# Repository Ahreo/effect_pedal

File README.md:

# effect_pedal

Guitar effect pedal with bluetooth connectivity!

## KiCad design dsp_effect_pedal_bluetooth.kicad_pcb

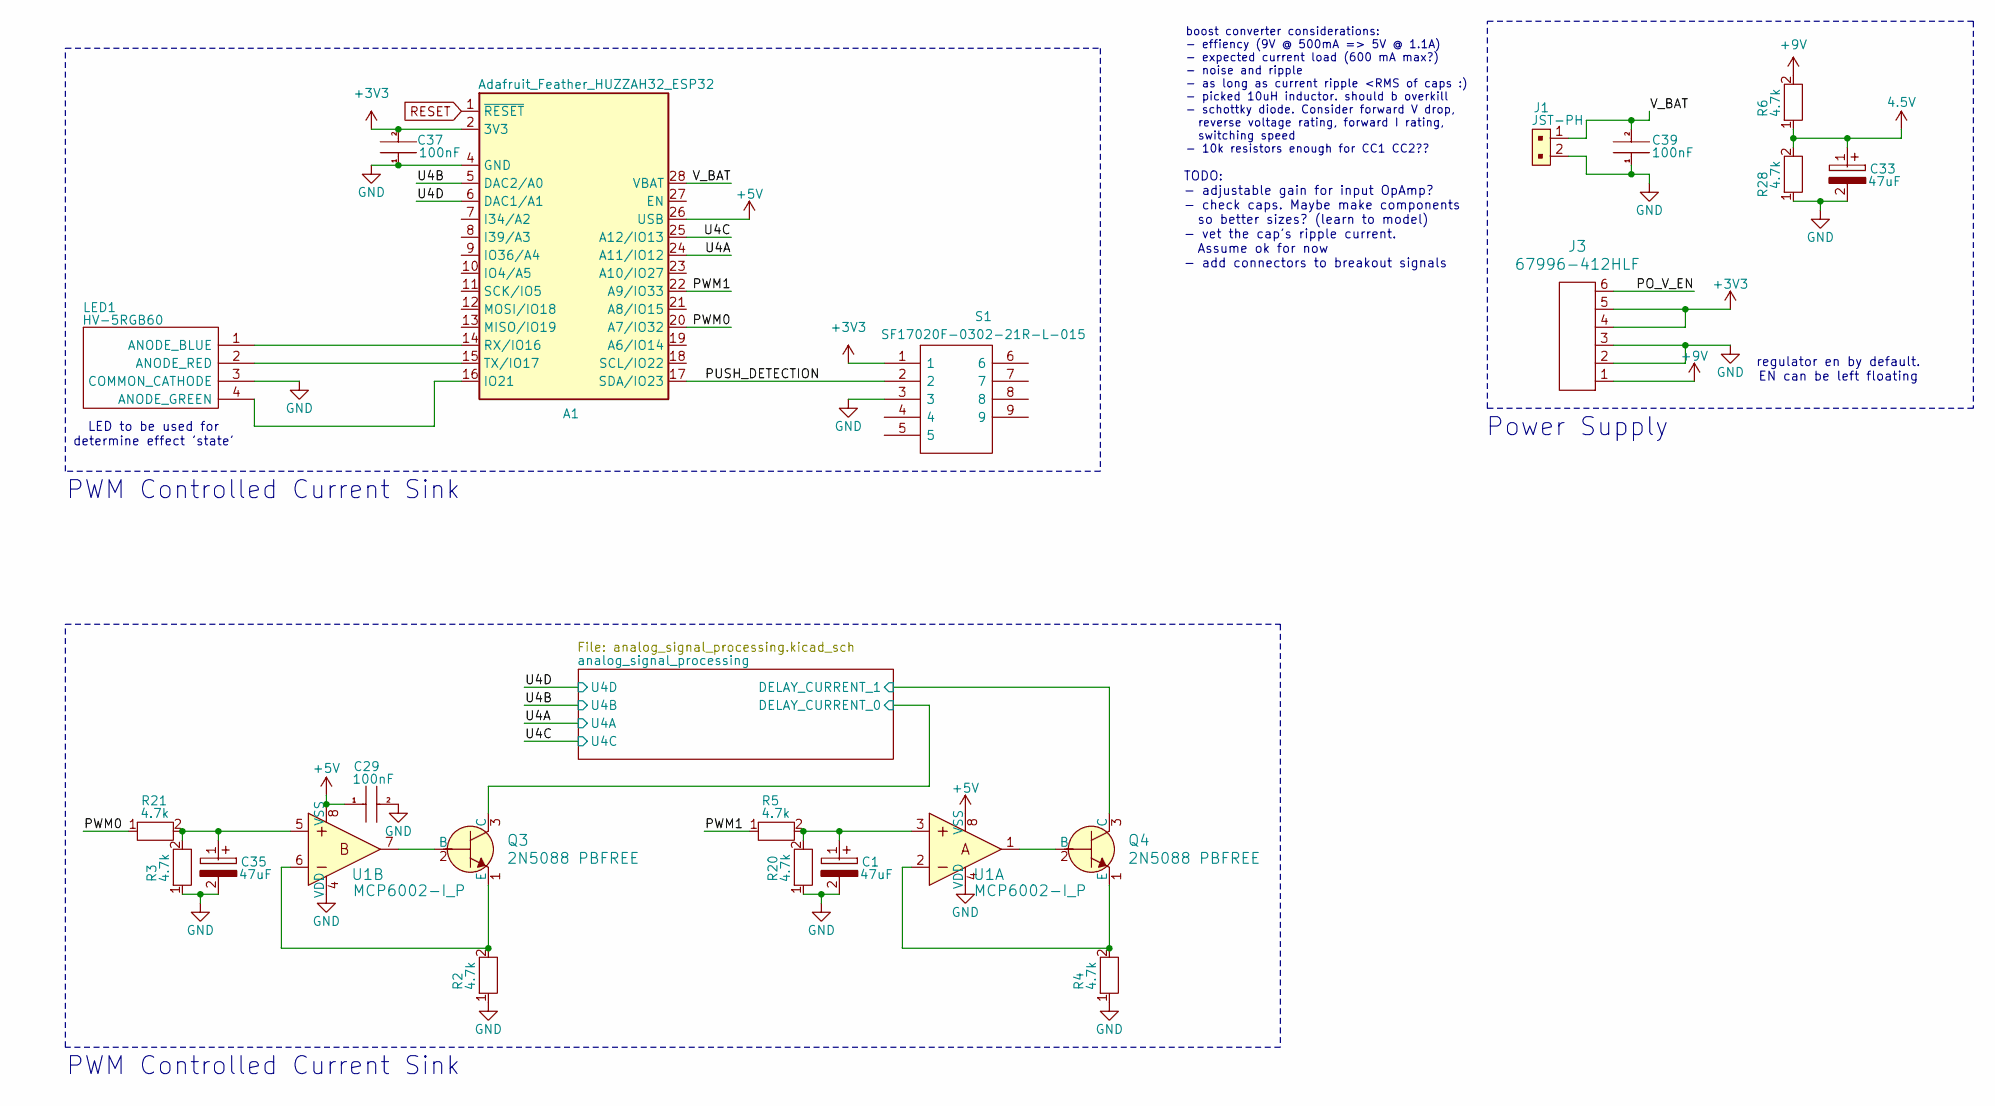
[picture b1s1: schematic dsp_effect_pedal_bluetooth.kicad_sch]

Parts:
A1: Adafruit_Feather_HUZZAH32_ESP32; Adafruit_Feather
C1, C33, C35: 47uF; 1206; Manufacturer_Part_Number REA470M1CBK-0511P; Mouser Part Number 140-REA470M1CBK0511P
C29, C37, C39: 100nF; 1206; Manufacturer_Part_Number SR211C104KARTR1; Mouser Part Number 581-SR211C104KARTR1
J1: JST-PH; PinHeader_1x2_P2mm_Drill1mm; MPN B2B-PH-K-S(LF)(SN); Digi-Key_PN 455-1704-ND
J3: 67996-412HLF; PinHeader_1x06_P2.54mm_Vertical; MPN 67996-412HLF; Digi-Key_PN 609-3219-ND
LED1: HV-5RGB60; HV5RGB25; Manufacturer_Part_Number HV-5RGB60; Mouser Part Number 743-HV-5RGB60
Q3, Q4: 2N5088 PBFREE; TO-92-3; MPN 2N5088BU; Digi-Key_PN 2N5088BU-ND
R2, R3, R4, R5, R6, R20, R21, R28: 4.7k; 1206; Manufacturer_Part_Number MFR-25FRF52-4K7; Mouser Part Number 603-MFR-25FRF52-4K7
S1: SF17020F-0302-21R-L-015; SF17020F030221RL015; Manufacturer_Part_Number SF17020F-0302-21R-L-015; Mouser Part Number 107-SF17020F-32-21RL
U1: MCP6002-I_P; DIP-8_W7.62mm; MPN MCP6002-I/P; Digi-Key_PN MCP6002-I/P-ND

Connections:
4.5V: C33.1, R6.1, R28.2; also elsewhere on the board
+3V3: A1.2 (3V3), C37.2, J3.4, J3.5, S1.1
+5V: A1.26 (USB), C29.1, U1.8 (VSS); also elsewhere on the board
+9V: J3.1, R6.2; also elsewhere on the board
/PO_V_EN: J3.6
/PUSH_DETECTION: A1.17 (SDA/IO23), S1.2
/PWM0: A1.20 (A7/IO32), R21.1
/PWM1: A1.22 (A9/IO33), R5.1
/U4A: A1.24 (A11/IO12); also elsewhere on the board
/U4B: A1.5 (DAC2/A0); also elsewhere on the board
/U4C: A1.25 (A12/IO13); also elsewhere on the board
/U4D: A1.6 (DAC1/A1); also elsewhere on the board
/V_BAT: A1.28 (VBAT), C39.2, J1.1
/analog_signal_processing/DELAY_CURRENT_0: Q3.3 (C); also elsewhere on the board
/analog_signal_processing/DELAY_CURRENT_1: Q4.3 (C); also elsewhere on the board
GND: A1.4 (GND), C1.2, C29.2, C33.2, C35.2, C37.1, C39.1, J1.2, J3.2, J3.3, LED1.3 (COMMON_CATHODE), R2.1, R3.1, R4.1, R20.1, R28.1, S1.3, U1.4 (VDD); also elsewhere on the board
unnamed: A1.16 (IO21), LED1.4 (ANODE_GREEN)
unnamed: A1.14 (RX/IO16), LED1.1 (ANODE_BLUE)
unnamed: A1.15 (TX/IO17), LED1.2 (ANODE_RED)
unnamed: C1.1, R5.2, R20.2, U1.3
unnamed: C35.1, R3.2, R21.2, U1.5
unnamed: Q3.2 (B), U1.7
unnamed: Q3.1 (E), R2.2, U1.6
unnamed: Q4.2 (B), U1.1
unnamed: Q4.1 (E), R4.2, U1.2
RESET: A1.1 (~RESET)

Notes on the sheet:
PWM Controlled Current Sink
LED to be used for determine effect 'state'
Power Supply
boost converter considerations: - effiency (9V @ 500mA => 5V @ 1.1A) - expected current load (600 mA max?) - noise and ripple - as long as current ripple <RMS of caps :) - picked 10uH inductor. should b overkill - schottky diode. Consider forward V drop, reverse voltage rating, forward I rating, sw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
regulator en by default. EN can be left floating
TODO: - adjustable gain for input OpAmp? - check caps. Maybe make components so better sizes? (learn to model) - vet the cap's ripple current. Assume ok for now - add connectors to breakout signals

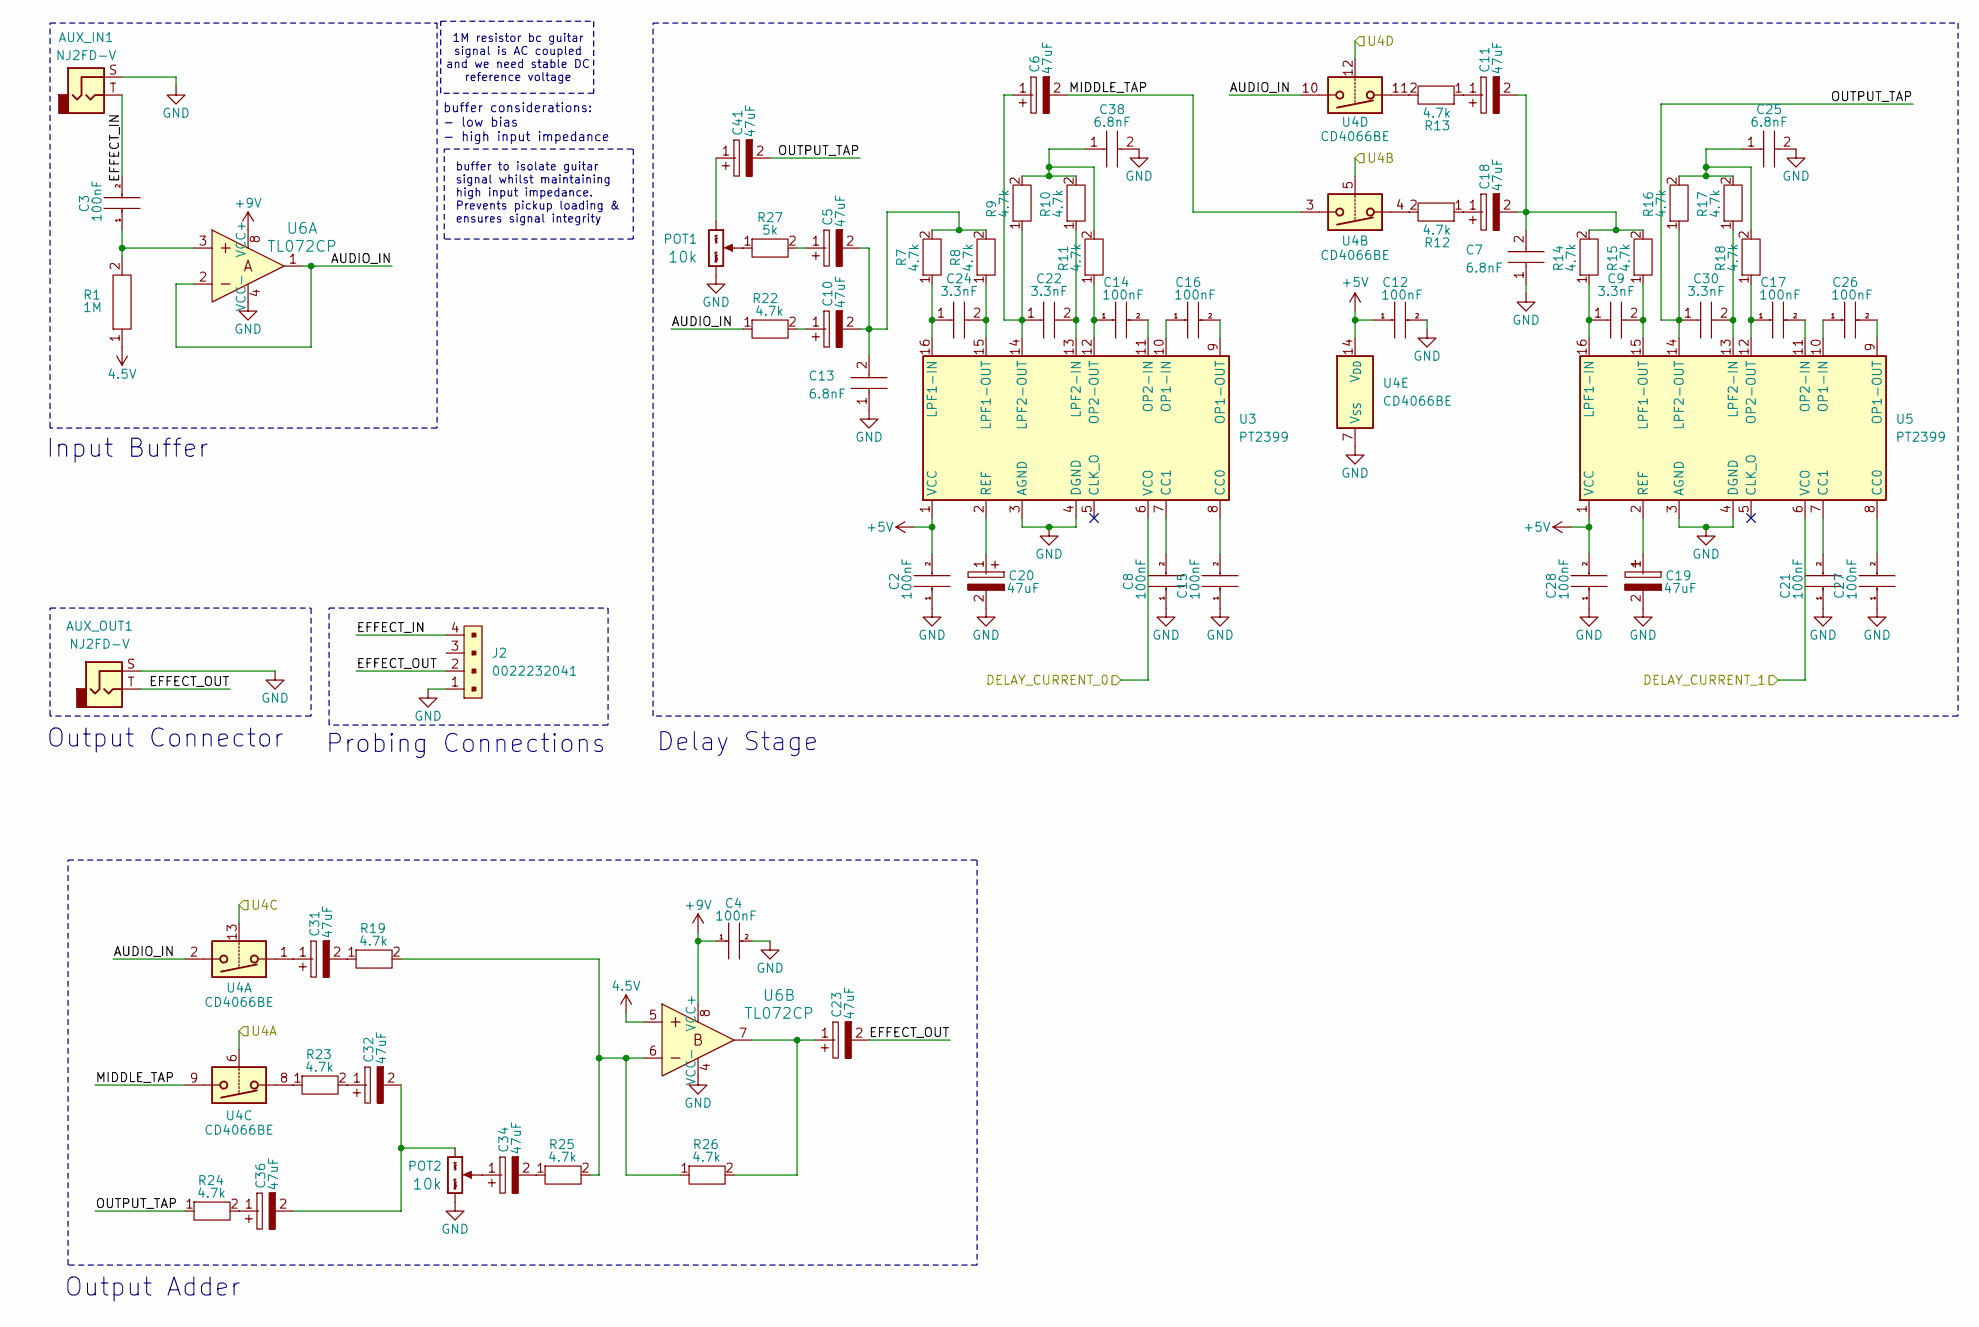
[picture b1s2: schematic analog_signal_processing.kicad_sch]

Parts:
AUX_IN1: NJ2FD-V; Jack_6.35mm_Neutrik_NJ2FD-V_Vertical
AUX_OUT1: NJ2FD-V; Jack_6.35mm_Neutrik_NJ2FD-V_Vertical
C2, C3, C4, C8, C12, C14, C15, C16, C17, C21, C26, C27, C28: 100nF; 1206; Manufacturer_Part_Number SR211C104KARTR1; Mouser Part Number 581-SR211C104KARTR1
C5, C6, C10, C11, C18, C19, C20, C23, C31, C32, C34, C36, C41: 47uF; 1206; Manufacturer_Part_Number REA470M1CBK-0511P; Mouser Part Number 140-REA470M1CBK0511P
C7, C13, C25, C38: 6.8nF; 1206; Manufacturer_Part_Number SR211C682MARTR1; Mouser Part Number 581-SR211C682MARTR1
C9, C22, C24, C30: 3.3nF; 1206; Manufacturer_Part_Number RCER72A332K0DBH03A
J2: 0022232041; PinHeader_1x4_P2.54mm_Drill1.02mm; MPN 0022232041; Digi-Key_PN WM4202-ND
POT1, POT2: 16mm_NoDet_10k; KRISTOF_POT; Part Number RV16AF-4A-15FW-B10k-3
R1: 1M; 1206; Manufacturer_Part_Number MFR-25FRF52-1M; Mouser Part Number 603-MFR-25FRF521M
R7, R8, R9, R10, R11, R12, R13, R14, R15, R16, R17, R18, R19, R22, R23, R24, R25, R26: 4.7k; 1206; Manufacturer_Part_Number MFR-25FRF52-4K7; Mouser Part Number 603-MFR-25FRF52-4K7
R27: 5k; 1206; Manufacturer_Part_Number YR1B4K99CC; Mouser Part Number 279-YR1B4K99CC
U3, U5: PT2399; DIP-16_W7.62mm
U4: CD4066BE; DIP-14_W7.62mm
U6: TL072CP; DIP-8_W7.62mm; MPN TL072CP; Digi-Key_PN 296-1775-5-ND

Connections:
4.5V: R1.1, U6.5; also elsewhere on the board
+5V: C2.2, C12.1, C28.2, U3.1 (VCC), U4.14 (V_{DD}), U5.1 (VCC); also elsewhere on the board
+9V: C4.1, U6.8 (VCC+); also elsewhere on the board
/U4A: U4.6; also elsewhere on the board
/U4B: U4.5; also elsewhere on the board
/U4C: U4.13; also elsewhere on the board
/U4D: U4.12; also elsewhere on the board
/analog_signal_processing/AUDIO_IN: R22.1, U4.2, U4.10, U6.1, U6.2
/analog_signal_processing/DELAY_CURRENT_0: U3.6 (VCO); also elsewhere on the board
/analog_signal_processing/DELAY_CURRENT_1: U5.6 (VCO); also elsewhere on the board
/analog_signal_processing/EFFECT_IN: AUX_IN1.T, C3.2, J2.4
/analog_signal_processing/EFFECT_OUT: AUX_OUT1.T, C23.2, J2.2
/analog_signal_processing/MIDDLE_TAP: C6.2, U4.3, U4.9
/analog_signal_processing/OUTPUT_TAP: C30.1, C41.2, R16.1, R24.1, U5.14 (LPF2-OUT)
GND: AUX_IN1.S, AUX_OUT1.S, C2.1, C4.2, C7.1, C8.1, C12.2, C13.1, C15.1, C19.2, C20.2, C21.1, C25.2, C27.1, C28.1, C38.2, J2.1, POT1.3 (Right), POT2.3 (Right), U3.3 (AGND), U3.4 (DGND), U4.7 (V_{SS}), U5.3 (AGND), U5.4 (DGND), U6.4 (VCC-); also elsewhere on the board
unnamed: C3.1, R1.2, U6.3
unnamed: C5.1, R27.2
unnamed: C10.1, R22.2
unnamed: C5.2, C10.2, C13.2, R7.2, R8.2
unnamed: C11.1, R13.1
unnamed: C7.2, C11.2, C18.2, R14.2, R15.2
unnamed: C18.1, R12.1
unnamed: C23.1, R26.2, U6.7
unnamed: C25.1, R16.2, R17.2, R18.2
unnamed: C31.1, U4.1
unnamed: C31.2, R19.1
unnamed: C32.1, R23.2
unnamed: C34.2, R25.1
unnamed: C36.1, R24.2
unnamed: C38.1, R9.2, R10.2, R11.2
unnamed: POT1.2 (Center), R27.1
unnamed: C41.1, POT1.1 (Left)
unnamed: C34.1, POT2.2 (Center)
unnamed: C32.2, C36.2, POT2.1 (Left)
unnamed: R12.2, U4.4
unnamed: R13.2, U4.11
unnamed: R19.2, R25.2, R26.1, U6.6
unnamed: R23.1, U4.8
unnamed: C15.2, U3.8 (CC0)
unnamed: C8.2, U3.7 (CC1)
unnamed: C24.1, R7.1, U3.16 (LPF1-IN)
unnamed: C24.2, R8.1, U3.15 (LPF1-OUT)
unnamed: C22.2, R10.1, U3.13 (LPF2-IN)
unnamed: C6.1, C22.1, R9.1, U3.14 (LPF2-OUT)
unnamed: C16.1, U3.10 (OP1-IN)
unnamed: C16.2, U3.9 (OP1-OUT)
unnamed: C14.2, U3.11 (OP2-IN)
unnamed: C14.1, R11.1, U3.12 (OP2-OUT)
unnamed: C20.1, U3.2 (REF)
unnamed: C27.2, U5.8 (CC0)
unnamed: C21.2, U5.7 (CC1)
unnamed: C9.1, R14.1, U5.16 (LPF1-IN)
unnamed: C9.2, R15.1, U5.15 (LPF1-OUT)
unnamed: C30.2, R17.1, U5.13 (LPF2-IN)
unnamed: C26.1, U5.10 (OP1-IN)
unnamed: C26.2, U5.9 (OP1-OUT)
unnamed: C17.2, U5.11 (OP2-IN)
unnamed: C17.1, R18.1, U5.12 (OP2-OUT)
unnamed: C19.1, U5.2 (REF)

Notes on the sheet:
Output Adder
Delay Stage
Probing Connections
1M resistor bc guitar signal is AC coupled and we need stable DC reference voltage
Input Buffer
Output Connector
buffer to isolate guitar signal whilst maintaining high input impedance. Prevents pickup loading & ensures signal integrity
buffer considerations: - low bias - high input impedance

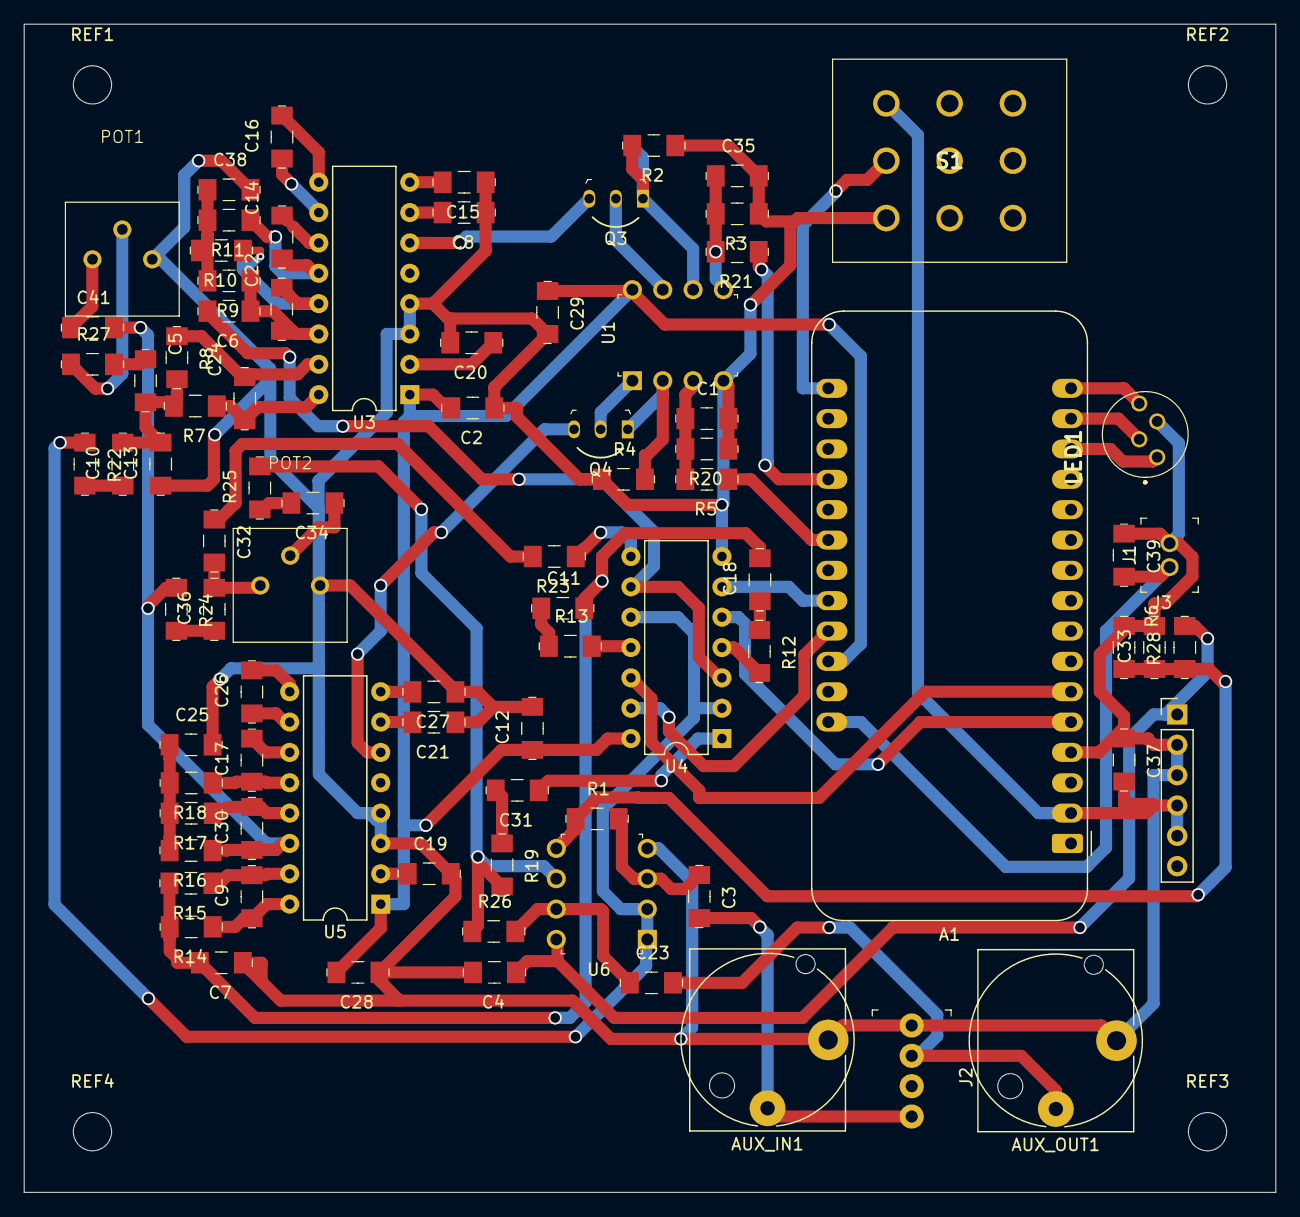
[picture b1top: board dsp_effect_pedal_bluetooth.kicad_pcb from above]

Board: 2 copper layers, 104.8 x 97.8 mm, 89 parts (0 on the bottom side), 73 nets.

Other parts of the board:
REF1, REF2, REF3, REF4: MountingHole_3.2mm_M3

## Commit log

2025-02-11 init commit
2025-02-19 input buffer
2025-02-19 step up converter work
2025-02-27 finished step up and analog input
2025-03-08 GIGA added. Delay stage + output adder schematics + hierarchy
2025-03-31 wip on esp conns
2025-04-07 fixed a lot of things
2025-05-09 initial board routing
